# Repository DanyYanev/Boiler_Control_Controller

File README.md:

# Boiler_Control_Controller

## Awards

Business choice award from <b>TelebidPro</b> at <b>TUES FEST</b>

## Assignment 
 
Developing an easy-to-use device for controlling complicated water-heating systems through relays, giving the end user the ability to easily manage the heating system by the provided local touchscreen display, or remotely done so by the developed mobile Android application.

## General Characteristics of the problem

The product allows the end-user to easily and quickly control the system while being very efficient on resources such as time, electricity and water and taking fault proof into consideration.
It’s especially useful when manging the heating system of a distanced house in an underpopulated location. Using this system frees you from the responsibility to go there and manually manage everything and allows you to quickly setup your heating system just in time before you arrive as if you were just there yesterday. 

## General Working Schema

  The whole system water-heating system is controlled by an Arduino Mega that communicates with an ESP8266 Module, the GUI is a [Nextion Display](https://nextion.itead.cc/) which is getting programmed through the Nextion Editor. All pictures were designed using Adobe Photoshop and are located in [here](/resourses/pictures/).

  The Arduino Mega and the ESP module communicate through regular serial. The serialEvent interrupt function in each controller parses the messages.

  The main functionality of the ESP module is to communicate with the API via HTTP requests. While the Mega is responsible for building the logic and managing the hardware. Both devises have acknowledgement whether or not a message has been parsed successfully.
		
  Every 10 seconds the ESP module attempts to fetch information from the server via a GET request at “[server_ulr]/users/[user_token]”. Every device has a unique user-generated user token and a controller token which is built in the ESP module and is unique for every microcontroller. After a successful request the body of the request is fetched and sent to the Mega controller. The body contains a JSON specified by the API Documentation here. If the parsing is successful the Mega controller will send an acknowledgement message. 

The ESP won’t send data to be parsed if the current running configuration is the same as the one fetched from the server.

After a local change is made the Mega will prepare a new JSON with the changes.

  Every 5 seconds if a change is made to the configuration, the updated JSON will be parsed to the ESP which will then wrap it in a PUT request and send it to the server. If an update is successful an acknowledgement message will be sent to the MEGA and the JSON object will be flushed. Else the MEGA will continue to send the updates every 5 seconds.

  All required variables for the logic to be built are saved in EEPROM. In case of power loss, on startup all variables are loaded from the local non-volatile memory.

Controller code for Boiler_Control project. ELSYS-2018

App Repo - https://github.com/DanyYanev/Boiler_Control_App

Server Repo - https://github.com/DanyYanev/Boiler_Control_Server

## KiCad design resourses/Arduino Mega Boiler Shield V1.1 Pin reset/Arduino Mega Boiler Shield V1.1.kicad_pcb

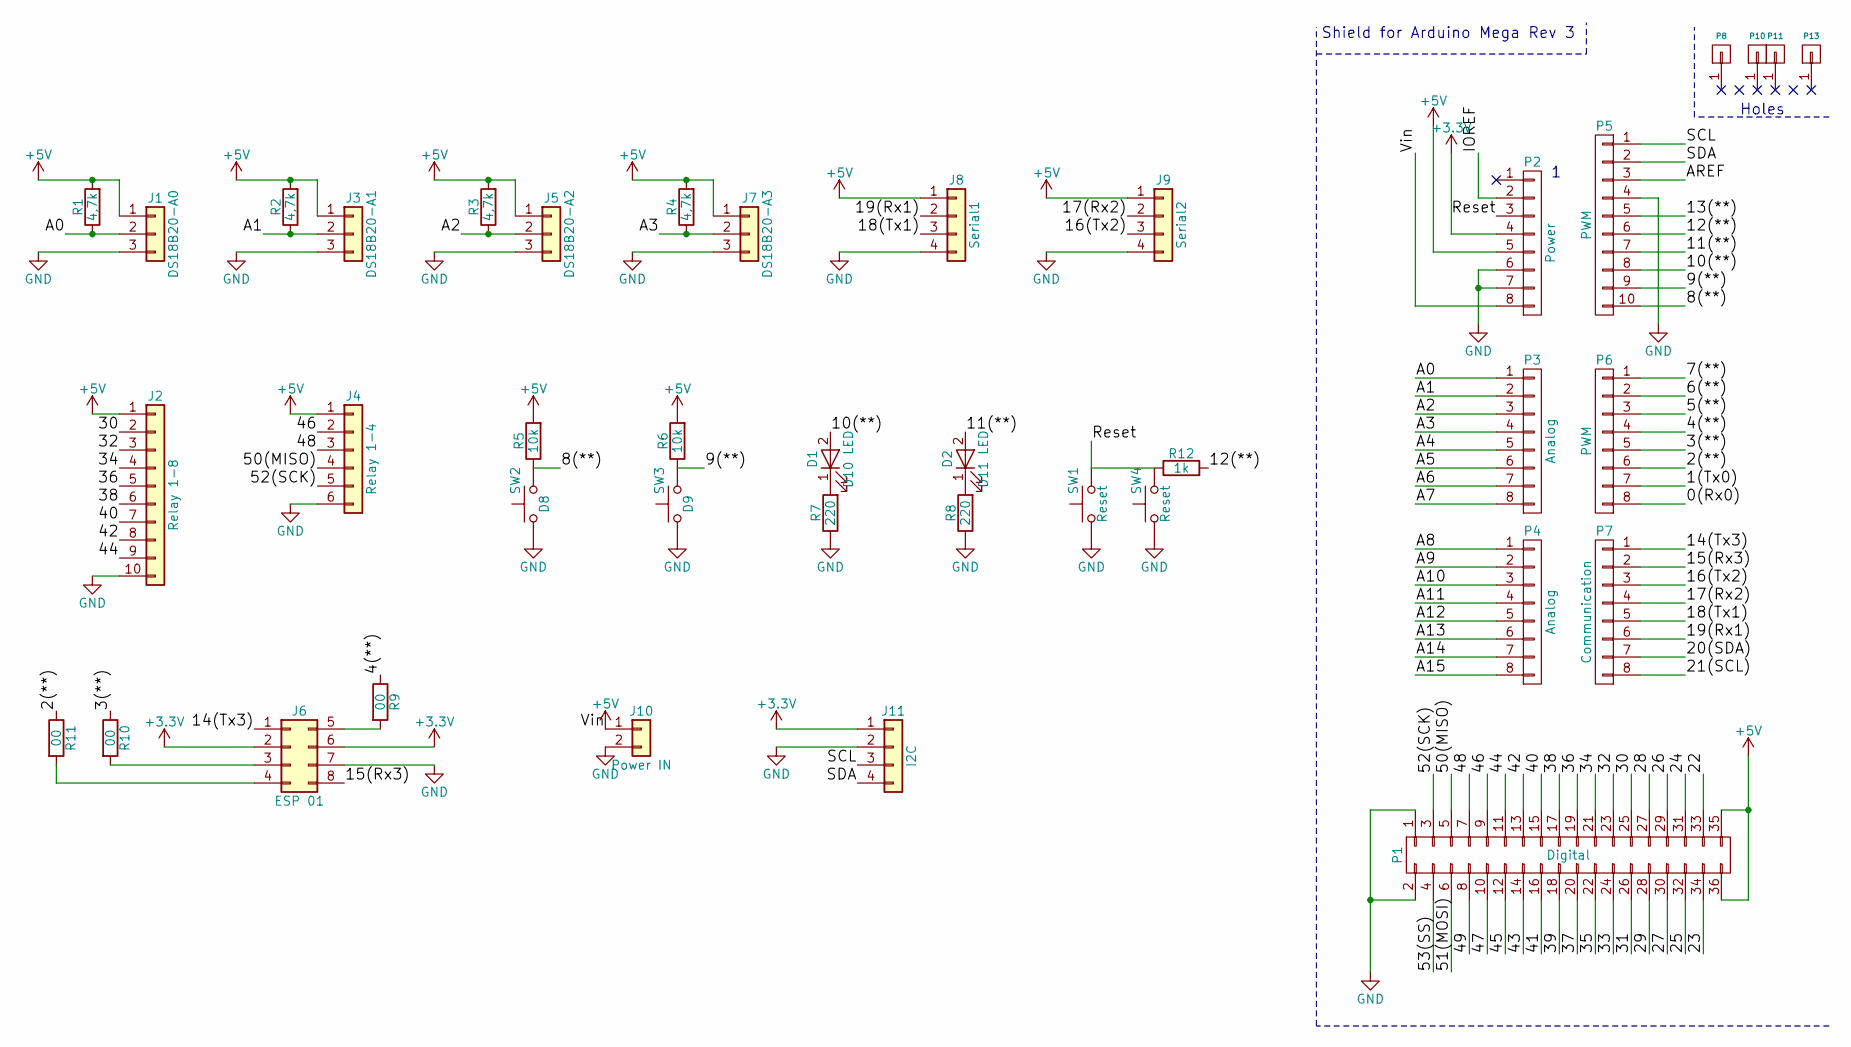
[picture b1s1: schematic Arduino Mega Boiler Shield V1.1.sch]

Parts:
D1: D10 LED; LED_1206_HandSoldering
D2: D11 LED; LED_1206_HandSoldering
J1: DS18B20-A0; JST_XH_B03B-XH-A_03x2.50mm_Straight
J2: Relay 1-8; JST_XH_B10B-XH-A_10x2.50mm_Straight
J3: DS18B20-A1; JST_XH_B03B-XH-A_03x2.50mm_Straight
J4: Relay 1-4; JST_XH_B06B-XH-A_06x2.50mm_Straight
J5: DS18B20-A2; JST_XH_B03B-XH-A_03x2.50mm_Straight
J6: ESP 01; Pin_Header_Straight_2x04_Pitch2.54mm
J7: DS18B20-A3; JST_XH_B03B-XH-A_03x2.50mm_Straight
J8: Serial1; JST_XH_B04B-XH-A_04x2.50mm_Straight
J9: Serial2; JST_XH_B04B-XH-A_04x2.50mm_Straight
J10: Power IN; JST_XH_B02B-XH-A_02x2.50mm_Straight
J11: I2C; JST_XH_B04B-XH-A_04x2.50mm_Straight
P1: Digital; Socket_Strip_Arduino_2x18
P2: Power; Socket_Strip_Arduino_1x08
P3, P4: Analog; Socket_Strip_Arduino_1x08
P5: PWM; Socket_Strip_Arduino_1x10
P6: PWM; Socket_Strip_Arduino_1x08
P7: Communication; Socket_Strip_Arduino_1x08
P8, P10, P11, P13: CONN_01X01; Arduino_1pin
R1, R2, R3, R4: 4,7k; R_1206_HandSoldering
R5, R6: 10k; R_1206_HandSoldering
R7, R8: 220; R_1206_HandSoldering
R9, R10, R11: 00; R_1206_HandSoldering
R12: 1k; R_1206_HandSoldering
SW1: Reset; SW_Tactile_SPST_Angled_PTS645Vx39-2LFS
SW2: D8; SW_PUSH_6mm_h5mm
SW3: D9; SW_PUSH_6mm_h5mm
SW4: Reset; SW_PUSH_6mm_h4.3mm

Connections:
+3V3: J6.2, J6.6, J11.1, P2.4
+5V: J1.1, J2.1, J3.1, J4.1, J5.1, J7.1, J8.1, J9.1, J10.1, P1.35, P1.36, P2.5, P2.8, R1.2, R2.2, R3.2, R4.2, R5.2, R6.2
/0(Rx0): P6.8
/1(Tx0): P6.7
/2(**): P6.6, R11.1
/3(**): P6.5, R10.1
/4(**): P6.4, R9.1
/5(**): P6.3
/6(**): P6.2
/7(**): P6.1
/8(**): P5.10, R5.1, SW2.2
/9(**): P5.9, R6.1, SW3.2
/10(**): D1.2 (A), P5.8
/11(**): D2.2 (A), P5.7
/12(**): P5.6, R12.2
/13(**): P5.5
/14(Tx3): J6.1, P7.1
/15(Rx3): J6.8, P7.2
/16(Tx2): J9.3, P7.3
/17(Rx2): J9.2, P7.4
/18(Tx1): J8.3, P7.5
/19(Rx1): J8.2, P7.6
/20(SDA): P7.7
/21(SCL): P7.8
/22: P1.33
/23: P1.34
/24: P1.31
/25: P1.32
/26: P1.29
/27: P1.30
/28: P1.27
/29: P1.28
/30: J2.2, P1.25
/31: P1.26
/32: J2.3, P1.23
/33: P1.24
/34: J2.4, P1.21
/35: P1.22
/36: J2.5, P1.19
/37: P1.20
/38: J2.6, P1.17
/39: P1.18
/40: J2.7, P1.15
/41: P1.16
/42: J2.8, P1.13
/43: P1.14
/44: J2.9, P1.11
/45: P1.12
/46: J4.2, P1.9
/47: P1.10
/48: J4.3, P1.7
/49: P1.8
/50(MISO): J4.4, P1.5
/51(MOSI): P1.6
/52(SCK): J4.5, P1.3
/53(SS): P1.4
/A0: J1.2, P3.1, R1.1
/A1: J3.2, P3.2, R2.1
/A2: J5.2, P3.3, R3.1
/A3: J7.2, P3.4, R4.1
/A4: P3.5
/A5: P3.6
/A6: P3.7
/A7: P3.8
/A8: P4.1
/A9: P4.2
/A10: P4.3
/A11: P4.4
/A12: P4.5
/A13: P4.6
/A14: P4.7
/A15: P4.8
/AREF: P5.3
/IOREF: P2.2
/Reset: P2.3, R12.1, SW1.2, SW4.2
/SCL: J11.3, P5.1
/SDA: J11.4, P5.2
GND: J1.3, J2.10, J3.3, J4.6, J5.3, J6.7, J7.3, J8.4, J9.4, J10.2, J11.2, P1.1, P1.2, P2.6, P2.7, P5.4, R7.1, R8.1, SW1.1, SW2.1, SW3.1, SW4.1
unnamed: D1.1 (K), R7.2
unnamed: D2.1 (K), R8.2
unnamed: J6.3, R10.2
unnamed: J6.4, R11.2
unnamed: J6.5, R9.2

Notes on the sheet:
Shield for Arduino Mega Rev 3
Holes

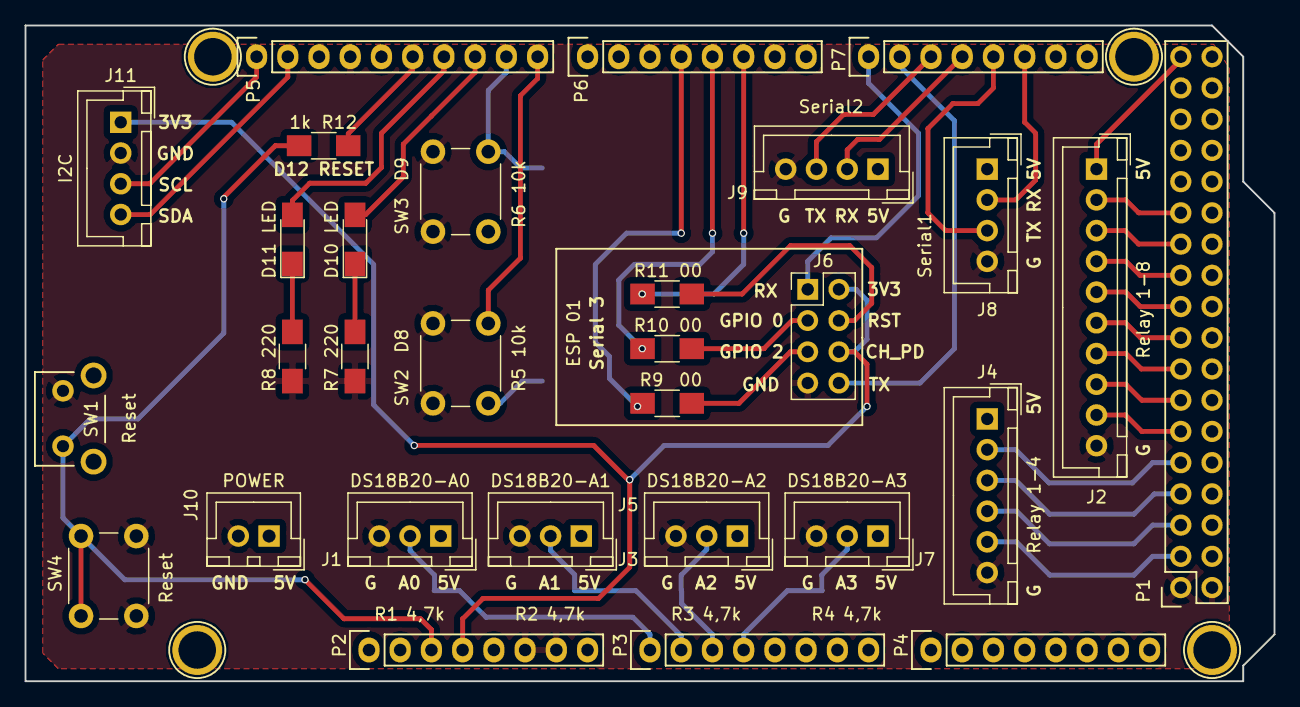
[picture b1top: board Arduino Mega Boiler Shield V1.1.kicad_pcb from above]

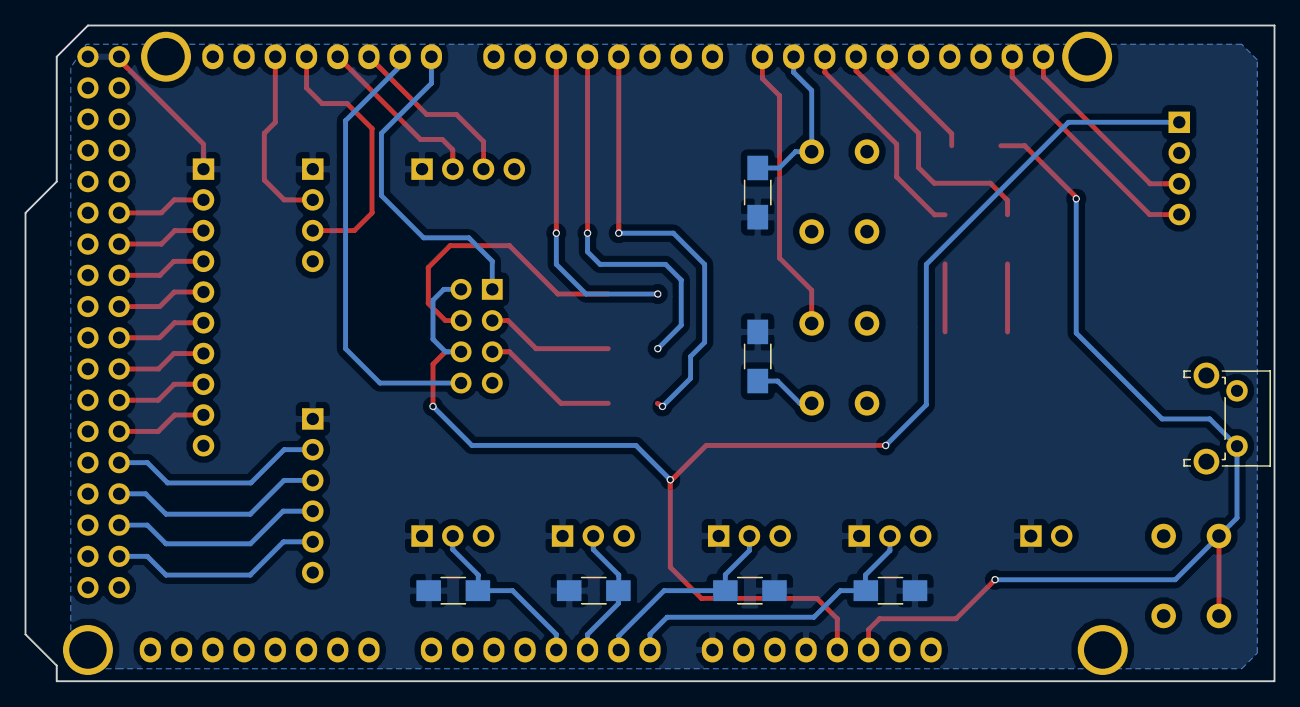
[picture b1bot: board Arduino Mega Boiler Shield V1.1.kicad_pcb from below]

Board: 2 copper layers, 101.6 x 53.3 mm, 40 parts (7 on the bottom side), 41 nets.

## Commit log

2017-04-10 shit got real
2017-04-11 All pumps working, awaits Main source control
2017-04-13 WORKING PRIORITY
2017-04-29 Finally working combined
2017-06-08 H file for func // not tested
2017-06-15 EEPROM
2017-07-20 small changes
2017-07-25 Boiler logistics fixed
2017-09-19 Unit tests
2017-09-19 To do list.
2017-09-19 Fixed bug, recreated lost Revision 3 Nextion file
2017-09-19 Added automatic clock update on the settings page, updates on debug messages
2017-09-19 All working
2017-09-19 Changed clocks, layout and working method
2017-09-19 removed useless files
2017-09-19 Added license
2017-09-19 Major repostory reorganization
2017-09-19 Revert "Major repostory reorganization"
2017-09-19 Major repository reorganization
2017-09-19 mass deletion of usless files
2017-09-19 more deletions
2017-09-19 readded license
2017-09-20 All pictures (archive)
2017-09-20 Archive removed, only latest pages
2017-09-20 fixed names
2017-09-22 Updated ToDoList
2017-09-23 Fixed bug with changed ids
2017-10-11 Everything working without boiler hist
2017-10-13 all working :)
2017-12-07 Bug fixed
2017-12-07 Fixed bug with heating state not getting remembered
2017-12-08 added funciton schematics and minor code changes
2018-02-15 Created readme
2018-02-20 fixed some errors in documentation
2018-02-26 Updated excel file and changed update algorithm
2018-02-26 Code refactoring - updated tempreture refreshing algorith to work way faster
2018-02-27 Updated Excell file
2018-02-27 ESP Code
    Added a bunch of code that still needs doing
2018-03-02 Fixed FloorPump not beeing affected by priority
2018-03-03 Successful get request with json response - vie http server
2018-03-09 Mega + ESP8266 successfully passing information to eachother
2018-03-11 Added functionalty to reset button, still doenst work :)
2018-03-11 Better temperature restrictions in case an eeprom error occurs
2018-03-11 Reset button works
2018-03-11 Not working esp reset for some reason, got latest updates from master onto esp branch
2018-03-26 Not tested code, should work tho (Wifi manager + http)
2018-03-27 Too embarassed to say what this commit is about
2018-04-28 working esp + ran main code
2018-05-24 Added full json parsing and esp - mega communication fully working
2018-05-27 Accepting data from server fully working
2018-05-27 Working json builder class
2018-05-27 Sending local changes to server
2018-05-27 ALL WORKING COMMIT
2018-05-28 New working scema - Mega - NodeMCU all working @9600
2018-05-30 Fixed race conditioning between locan and cloud updates, added message transmittion and verification
2018-05-30 Hot fixes and more confirmation of actions
2018-05-30 Removeing usless comments
2018-06-04 Added shield, and pngs
2018-06-04 Some spreadsheet changes?
2018-06-05 Documentation
2018-06-14 Updated readme after merge
2018-06-14 Fixed flushing
2018-06-14 Fixed merge bugs
